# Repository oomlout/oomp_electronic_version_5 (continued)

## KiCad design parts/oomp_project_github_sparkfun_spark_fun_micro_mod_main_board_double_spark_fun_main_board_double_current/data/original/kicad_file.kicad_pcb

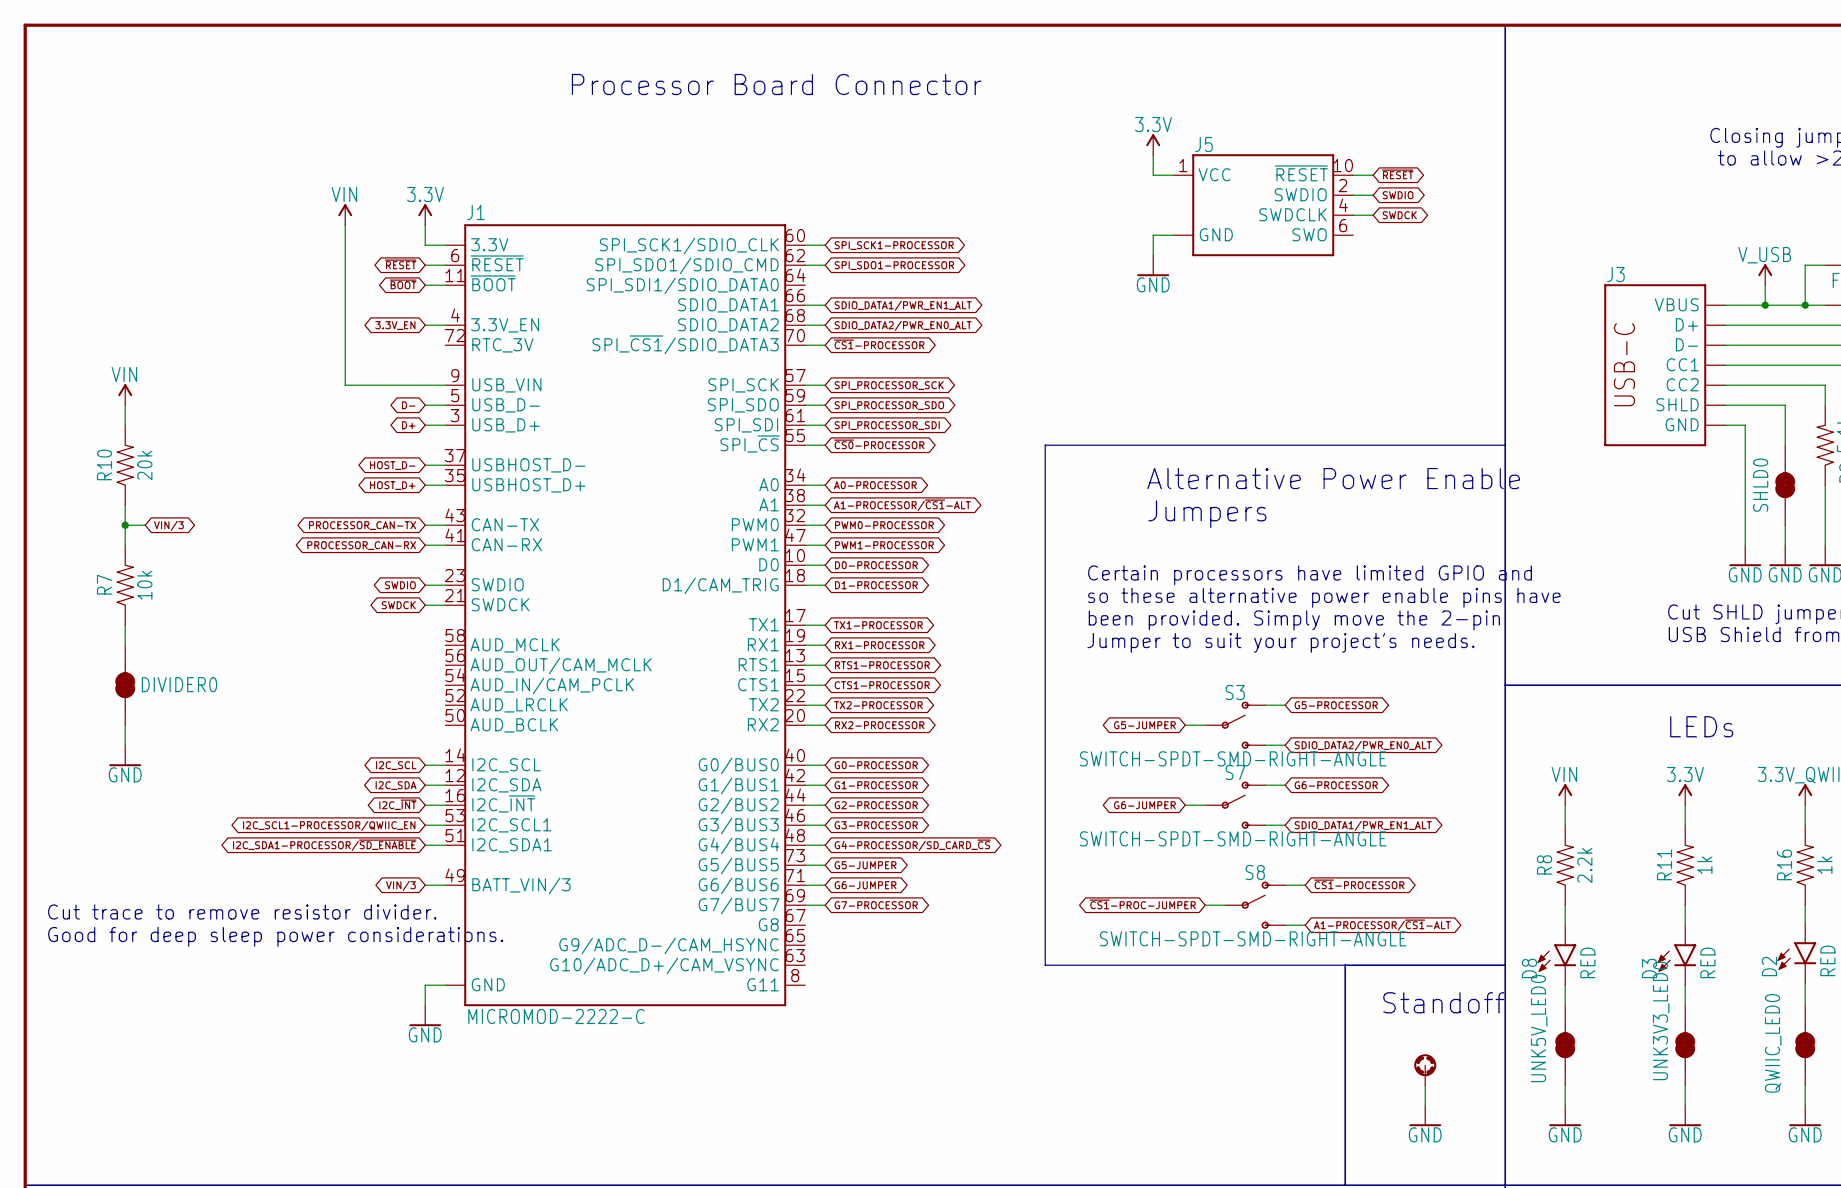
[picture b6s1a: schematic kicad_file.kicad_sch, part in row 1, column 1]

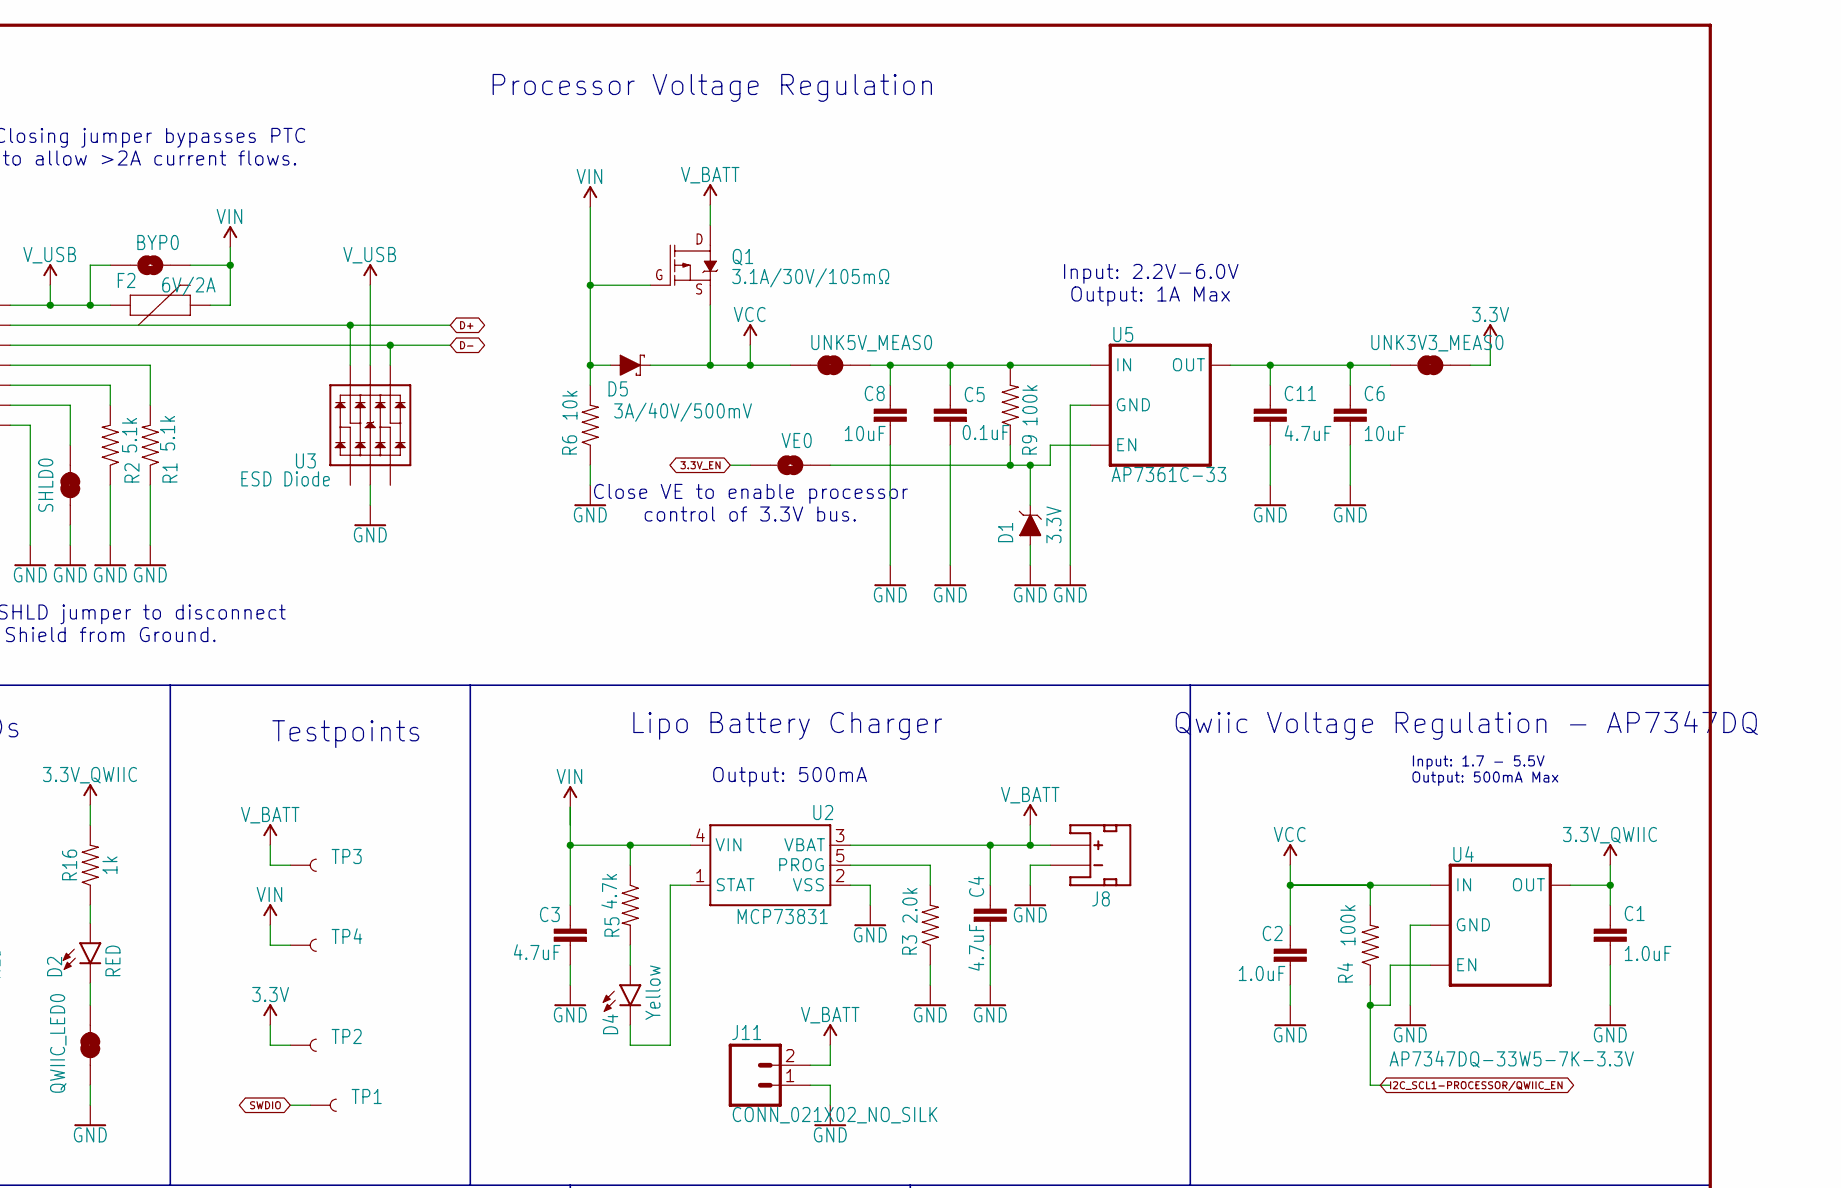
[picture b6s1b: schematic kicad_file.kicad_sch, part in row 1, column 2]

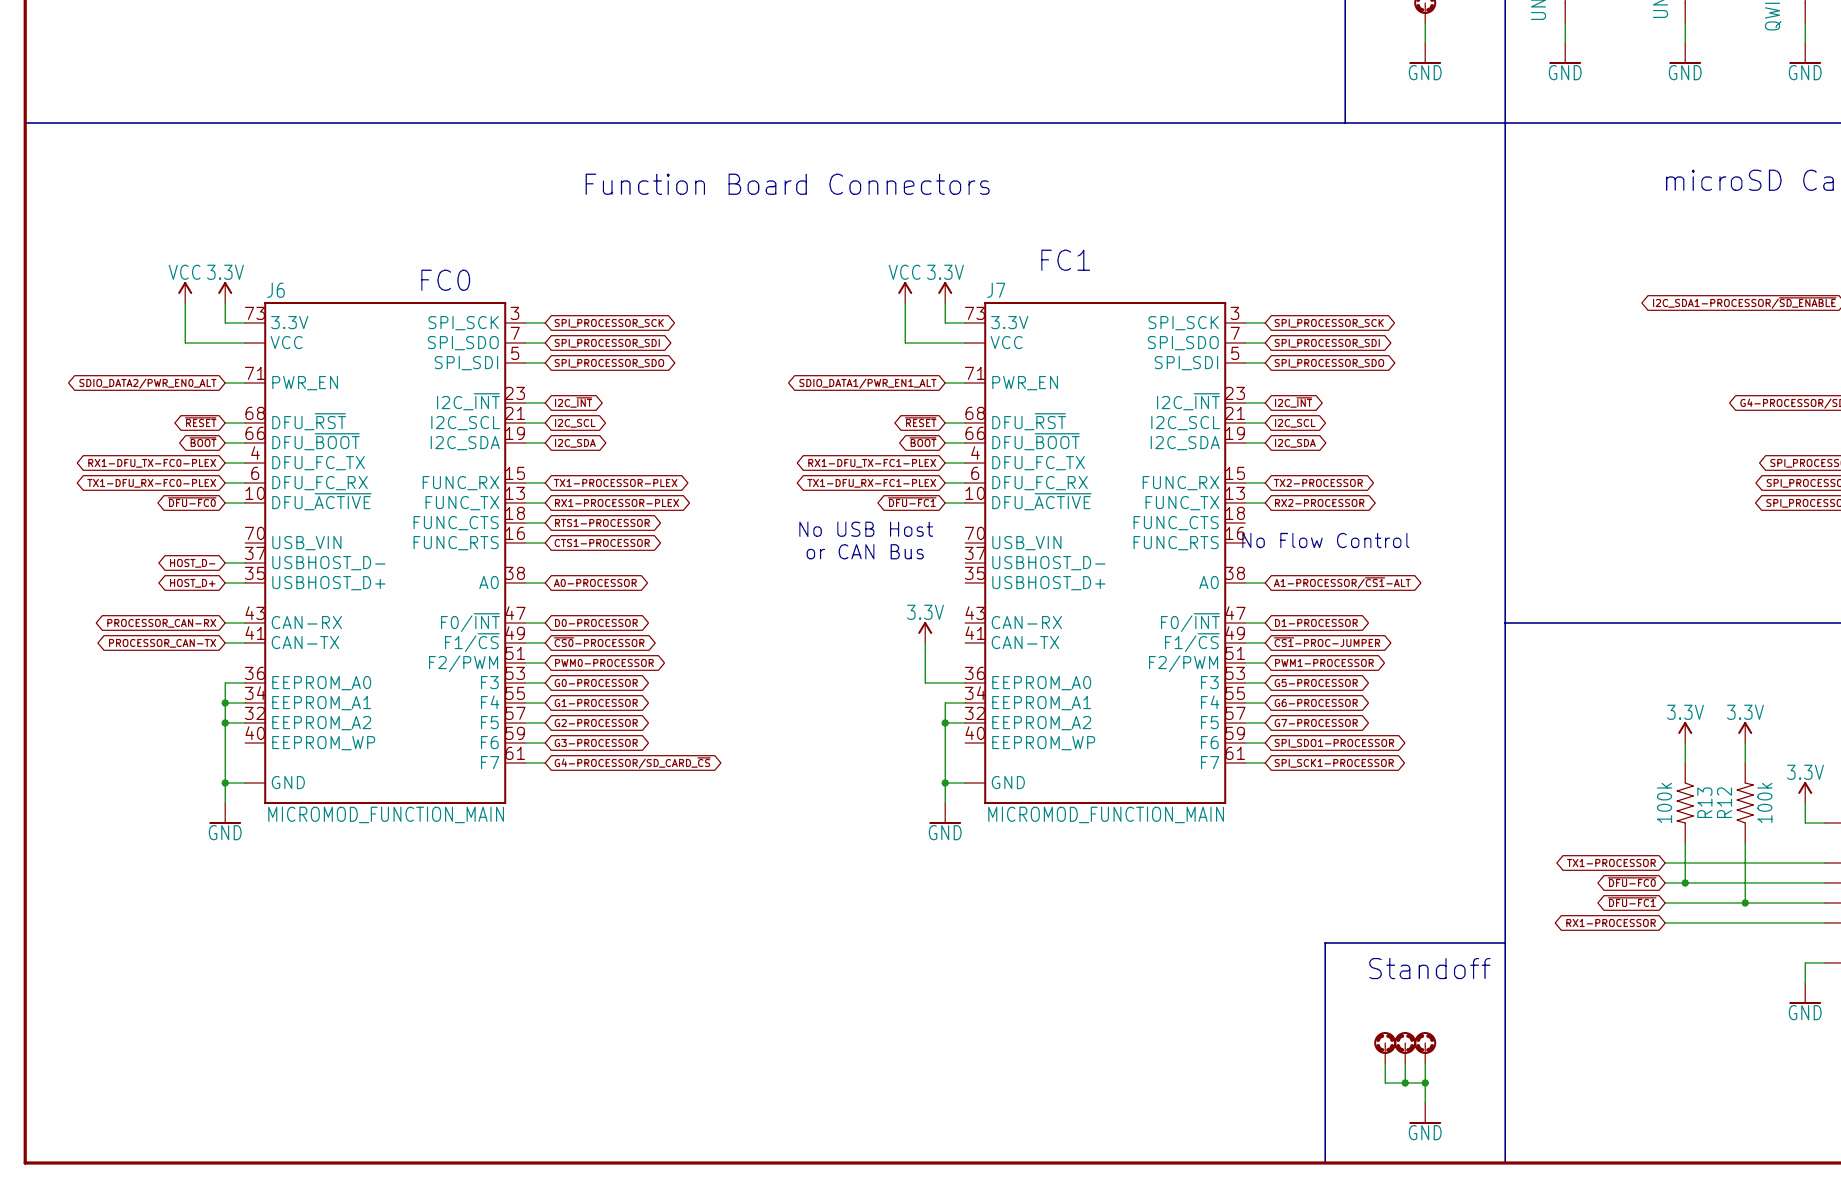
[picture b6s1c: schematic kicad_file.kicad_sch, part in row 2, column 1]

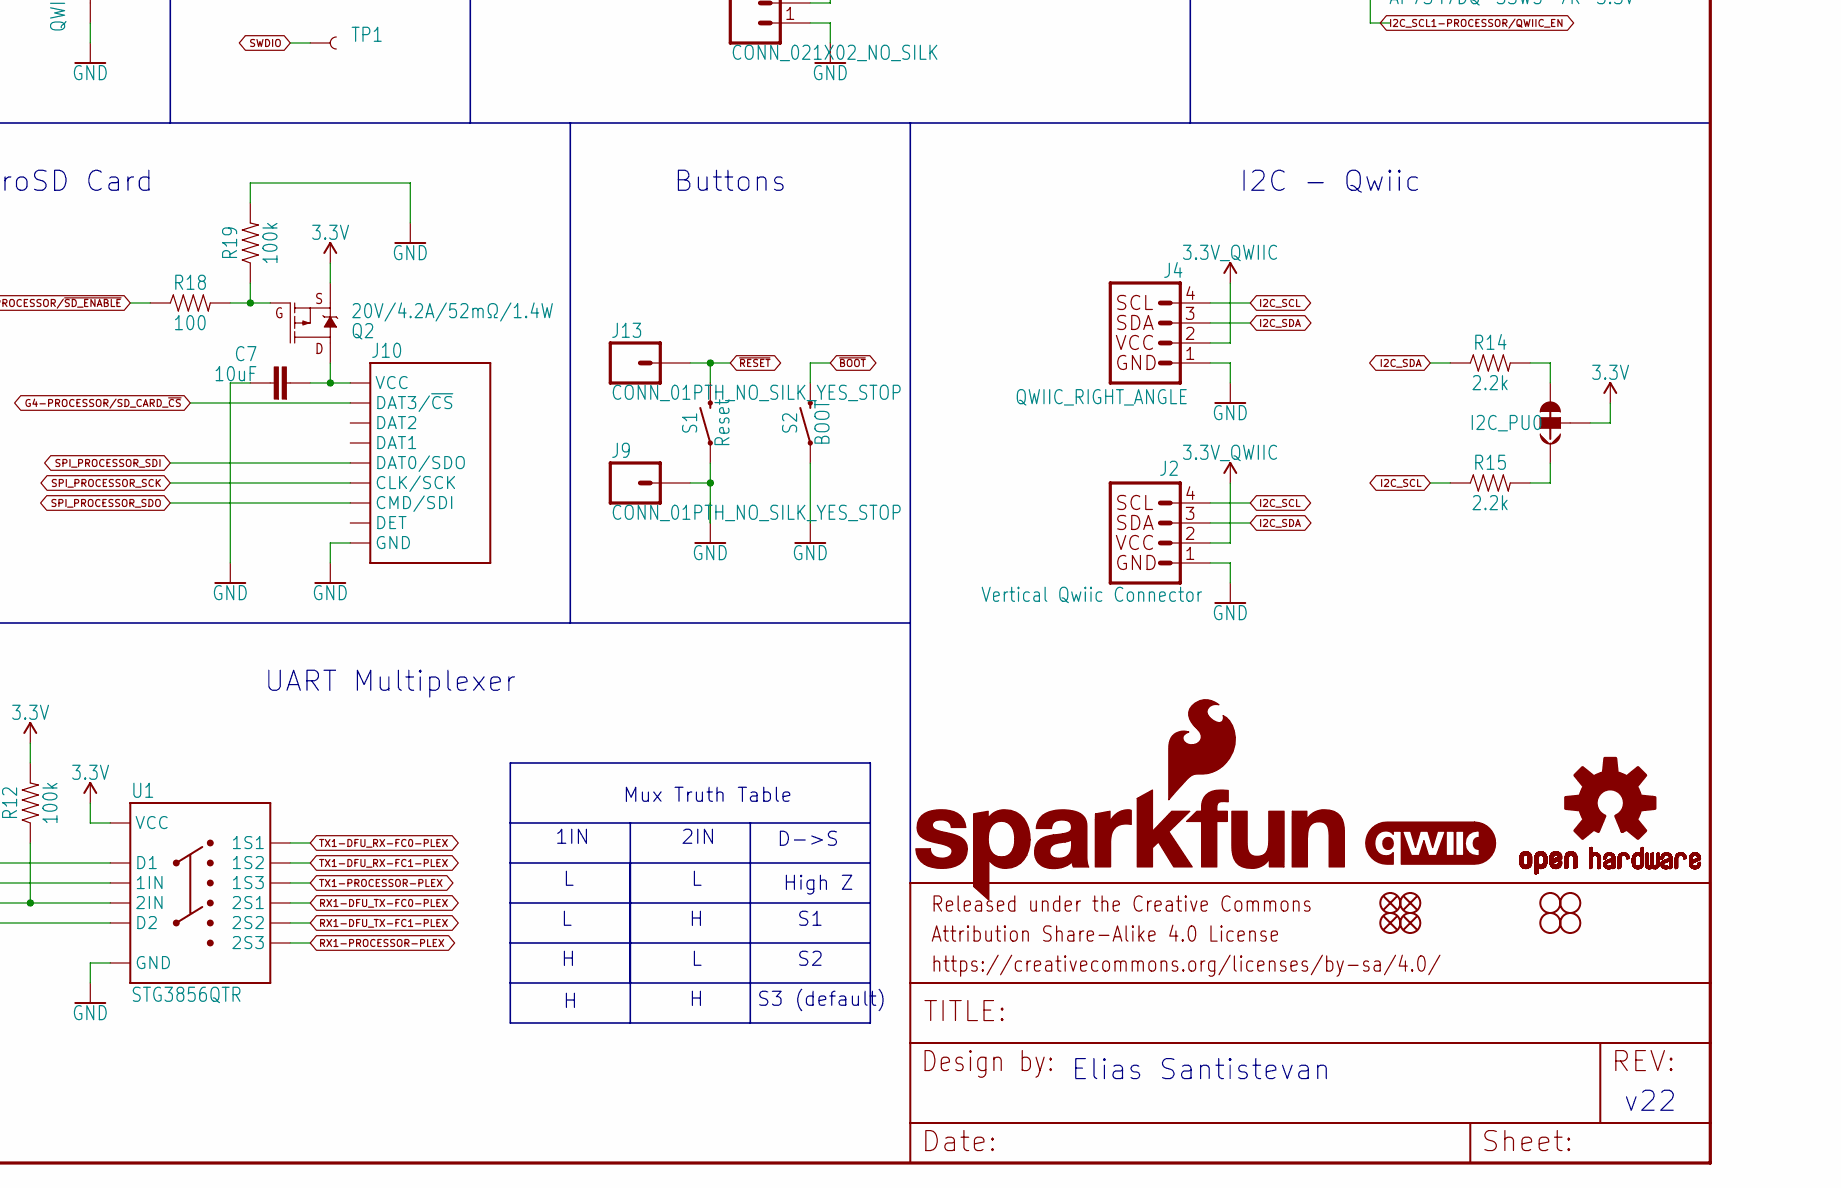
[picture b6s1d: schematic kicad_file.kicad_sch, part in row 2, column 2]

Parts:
BYP0: JUMPER-SMT_2_NO_SILK; SMT-JUMPER_2_NO_SILK
C1, C2: 1.0uF; 0603
C3, C4, C11: 4.7uF; 0603
C5: 0.1uF; 0603
C6, C8: 10uF; 0805
C7: 10uF; 0603
D1: 3.3V; SOD-323
D2, D3, D8: RED; LED-0603
D4: Yellow; LED-0603
D5: 3A/40V/500mV; SMA-DIODE
DIVIDER0: JUMPER-SMT_2_NC_TRACE_SILK; SMT-JUMPER_2_NC_TRACE_SILK
F2: 6V/2A; 1210
FD1, FD2, FD3, FD4: FIDUCIAL1X2; FIDUCIAL-1X2
FRAME1: FRAME-LEDGER; CREATIVE_COMMONS
H2, H3, H4, H8: STAND-OFF-REFLOW-M2.5_2.5MM_TALL; STAND-OFF-REFLOW-M2.5
H14, H15, H16, H17: STAND-OFFTIGHT; STAND-OFF-TIGHT
I2C_PU0: JUMPER-SMT_3_2-NC_TRACE_SILK; SMT-JUMPER_3_2-NC_TRACE_SILK
J1: MICROMOD-2222-C; M.2-CONNECTOR-E
J2: Vertical Qwiic Connector; JST04_1MM_VERT
J3: USB_C_2-LAYER_PADS; USB-C-16P-2LAYER-PADS
J4: QWIIC_RIGHT_ANGLE; JST04_1MM_RA
J5: CORTEX_JTAG_DEBUG_MINIMUM_PTH; 2X5-PTH-1.27MM
J6, J7: MICROMOD_FUNCTION_MAIN; M.2-CONNECTOR-E-FUNCTION-STANDARD
J8: JST_2MM_MALE; JST-2-SMD
J9, J13: CONN_01PTH_NO_SILK_YES_STOP; 1X01_NO_SILK
J10: MICRO-SD-PUSH-PUSH-EXT-PIN; MICROSD-EXTERNALPIN
J11: CONN_021X02_NO_SILK; 1X02_NO_SILK
LOGO1: QWIIC_LOGO_8MM; QWIIC_8MM
LOGO2: SFE_LOGO_NAME_FLAME.3_INCH; SFE_LOGO_NAME_FLAME_.3
LOGO3: OSHW-LOGOL; OSHW-LOGO-L
Q1: 3.1A/30V/105mΩ; SOT23-3
Q2: 20V/4.2A/52mΩ/1.4W; SOT23-3
QWIIC_LED0: JUMPER-SMT_2_NC_TRACE_SILK; SMT-JUMPER_2_NC_TRACE_SILK
R1, R2: 5.1k; 0603
R3: 2.0k; 0603
R4, R9, R12, R13, R19: 100k; 0603
R5: 4.7k; 0603
R6, R7: 10k; 0603
R8, R14, R15: 2.2k; 0603
R10: 20k; 0603
R11, R16: 1k; 0603
R18: 100; 0603
S1: Reset; TACTILE_SWITCH_SMD_5.2MM
S2: BOOT; TACTILE_SWITCH_SMD_5.2MM
S3, S7, S8: SWITCH-SPDT-SMD-RIGHT-ANGLE; SWITCH_SPST_SMD_A
SHLD0: JUMPER-SMT_2_NC_TRACE_SILK; SMT-JUMPER_2_NC_TRACE_SILK
TP1, TP2, TP3, TP4: TEST-POINT3X5; PAD.03X.05
U1: STG3856QTR; STG3856
U2: MCP73831; SOT23-5
U3: ESD Diode; SOT-23-6
U4: AP7347DQ-33W5-7K-3.3V; SOT25
U5: AP7361C-33; UDFN-8
UNK3V3_LED0, UNK5V_LED0: JUMPER-SMT_2_NC_TRACE_SILK; SMT-JUMPER_2_NC_TRACE_SILK
UNK3V3_MEAS0, UNK5V_MEAS0: JUMPER-COMBO_2_NC_TRACE; COMBO-JUMPER_2_NC_TRACE
VE0: JUMPER-SMT_2_NO_SILK; SMT-JUMPER_2_NO_SILK

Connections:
3.3V: I2C_PU0.2, J1.2 (3.3V), J1.74 (3.3V), J5.1 (VCC), J6.73 (3.3V), J7.36 (EEPROM_A0), J7.73 (3.3V), Q2.2 (S), R11.2, R12.2, R13.1, TP2.1, U1.P11 (VCC), UNK3V3_MEAS0.2, UNK3V3_MEAS0.4 (2)
3.3V_EN: J1.4 (3.3V_EN), VE0.1
3.3V_EN_VE: D1.C, R9.1, U5.5 (EN), VE0.2
3.3V_QWIIC: C1.1, J2.2, J4.2, R16.2, U4.5 (OUT)
3V3_MEAS: C6.1, C11.1, U5.1 (OUT), UNK3V3_MEAS0.1, UNK3V3_MEAS0.3 (1)
5V_MEAS: C5.1, C8.1, R9.2, U5.8 (IN), UNK5V_MEAS0.2, UNK5V_MEAS0.4 (2)
A0-PROCESSOR: J1.34 (A0), J6.38 (A0)
A1-PROCESSOR/~CS1-ALT: J1.38 (A1), J7.38 (A0), S8.3 (S)
CTS1-PROCESSOR: J1.15 (CTS1), J6.16 (FUNC_RTS)
D0-PROCESSOR: J1.10 (D0), J6.47 (F0/~INT)
D1-PROCESSOR: J1.18 (D1/CAM_TRIG), J7.47 (F0/~INT)
D+: J1.3 (USB_D+), J3.A6 (D+), J3.B6 (D+), U3.6 (IO4)
D-: J1.5 (USB_D-), J3.A7 (D-), J3.B7 (D-), U3.4 (IO3)
G0-PROCESSOR: J1.40 (G0/BUS0), J6.53 (F3)
G1-PROCESSOR: J1.42 (G1/BUS1), J6.55 (F4)
G2-PROCESSOR: J1.44 (G2/BUS2), J6.57 (F5)
G3-PROCESSOR: J1.46 (G3/BUS3), J6.59 (F6)
G4-PROCESSOR/SD_CARD_~CS: J1.48 (G4/BUS4), J6.61 (F7), J10.2 (DAT3/~CS)
G5-JUMPER: J1.73 (G5/BUS5), S3.2
G5-PROCESSOR: J7.53 (F3), S3.1 (O)
G6-JUMPER: J1.71 (G6/BUS6), S7.2
G6-PROCESSOR: J7.55 (F4), S7.1 (O)
G7-PROCESSOR: J1.69 (G7/BUS7), J7.57 (F5)
GND: C1.2, C2.2, C3.2, C4.2, C5.2, C6.2, C7.1, C8.2, C11.2, D1.A, DIVIDER0.1, H2.1, H3.1, H4.1, H8.1, J1.1 (GND), J1.7 (GND), J1.33 (GND), J1.36 (GND), J1.39 (GND), J1.45 (GND), J1.75 (GND), J2.1, J3.GND, J3.GND2 (GND), J4.1, J5.3 (GND), J5.5 (GND), J5.9 (GND), J6.1 (GND), J6.2 (GND), J6.8 (GND), J6.32 (EEPROM_A2), J6.33 (GND), J6.34 (EEPROM_A1), J6.36 (EEPROM_A0), J6.39 (GND), J6.45 (GND), J6.75 (GND), J7.1 (GND), J7.2 (GND), J7.8 (GND), J7.32 (EEPROM_A2), J7.33 (GND), J7.34 (EEPROM_A1), J7.39 (GND), J7.45 (GND), J7.75 (GND), J8.1 (-), J9.1, J10.6 (GND), J10.10 (GND), J10.11 (GND), J10.12 (GND), J10.13 (GND), J11.1, QWIIC_LED0.1, R1.1, R2.1, R3.1, R6.1, R19.2, S1.1, S1.2 (1), S2.1, S2.2 (1), SHLD0.1, U1.P5 (GND), U2.2 (VSS), U3.2 (VSS), U4.2 (GND), U5.4 (GND), U5.EP (GND), UNK3V3_LED0.1, UNK5V_LED0.1
HOST_D+: J1.35 (USBHOST_D+), J6.35 (USBHOST_D+)
HOST_D-: J1.37 (USBHOST_D-), J6.37 (USBHOST_D-)
I2C_SCL: J1.14 (I2C_SCL), J2.4, J4.4, J6.21 (I2C_SCL), J7.21 (I2C_SCL), R15.1
I2C_SCL1-PROCESSOR/QWIIC_EN: J1.53 (I2C_SCL1), R4.1, U4.3 (EN)
I2C_SDA: J1.12 (I2C_SDA), J2.3, J4.3, J6.19 (I2C_SDA), J7.19 (I2C_SDA), R14.1
I2C_SDA1-PROCESSOR/~SD_ENABLE: J1.51 (I2C_SDA1), R18.1
I2C_~INT: J1.16 (I2C_~INT), J6.23 (I2C_~INT), J7.23 (I2C_~INT)
unnamed: D4.A, R5.2
unnamed: D8.C, UNK5V_LED0.2
unnamed: D3.A, R11.1
unnamed: J3.B5 (CC2), R2.2
unnamed: J3.A5 (CC1), R1.2
unnamed: R3.2, U2.5 (PROG)
unnamed: DIVIDER0.2, R7.1
unnamed: D2.C, QWIIC_LED0.2
unnamed: D2.A, R16.1
unnamed: D3.C, UNK3V3_LED0.2
unnamed: I2C_PU0.3, R14.2
unnamed: D8.A, R8.1
unnamed: I2C_PU0.1, R15.2
unnamed: D4.C, U2.1 (STAT)
unnamed: C7.2, J10.4 (VCC), Q2.3 (D)
unnamed: Q2.1 (G), R18.2, R19.1
PROCESSOR_CAN-RX: J1.41 (CAN-RX), J6.43 (CAN-RX)
PROCESSOR_CAN-TX: J1.43 (CAN-TX), J6.41 (CAN-TX)
PWM0-PROCESSOR: J1.32 (PWM0), J6.51 (F2/PWM)
PWM1-PROCESSOR: J1.47 (PWM1), J7.51 (F2/PWM)
RTS1-PROCESSOR: J1.13 (RTS1), J6.18 (FUNC_CTS)
RX1-DFU_TX-FC0-PLEX: J6.4 (DFU_FC_TX), U1.P9 (2S1)
RX1-DFU_TX-FC1-PLEX: J7.4 (DFU_FC_TX), U1.P8 (2S2)
RX1-PROCESSOR: J1.19 (RX1), U1.P6 (D2)
RX1-PROCESSOR-PLEX: J6.13 (FUNC_TX), U1.P7 (2S3)
RX2-PROCESSOR: J1.20 (RX2), J7.13 (FUNC_TX)
SDIO_DATA1/PWR_EN1_ALT: J1.66 (SDIO_DATA1), J7.71 (PWR_EN), S7.3 (S)
SDIO_DATA2/PWR_EN0_ALT: J1.68 (SDIO_DATA2), J6.71 (PWR_EN), S3.3 (S)
SHLD: J3.SHLD1 (SHLD), J3.SHLD2 (SHLD), J3.SHLD3 (SHLD), J3.SHLD4 (SHLD), SHLD0.2
SPI_PROCESSOR_SCK: J1.57 (SPI_SCK), J6.3 (SPI_SCK), J7.3 (SPI_SCK), J10.5 (CLK/SCK)
SPI_PROCESSOR_SDI: J1.61 (SPI_SDI), J6.7 (SPI_SDO), J7.7 (SPI_SDO), J10.7 (DAT0/SDO)
SPI_PROCESSOR_SDO: J1.59 (SPI_SDO), J6.5 (SPI_SDI), J7.5 (SPI_SDI), J10.3 (CMD/SDI)
SPI_SCK1-PROCESSOR: J1.60 (SPI_SCK1/SDIO_CLK), J7.61 (F7)
SPI_SDO1-PROCESSOR: J1.62 (SPI_SDO1/SDIO_CMD), J7.59 (F6)
SWDCK: J1.21 (SWDCK), J5.4 (SWDCLK)
SWDIO: J1.23 (SWDIO), J5.2 (SWDIO), TP1.1
TX1-DFU_RX-FC0-PLEX: J6.6 (DFU_FC_RX), U1.P1 (1S1)
TX1-DFU_RX-FC1-PLEX: J7.6 (DFU_FC_RX), U1.P2 (1S2)
TX1-PROCESSOR: J1.17 (TX1), U1.P4 (D1)
TX1-PROCESSOR-PLEX: J6.15 (FUNC_RX), U1.P3 (1S3)
TX2-PROCESSOR: J1.22 (TX2), J7.15 (FUNC_RX)
VCC: C2.1, D5.C, J6.72 (VCC), J6.74 (VCC), J7.72 (VCC), J7.74 (VCC), Q1.2 (S), R4.2, U4.1 (IN), UNK5V_MEAS0.1, UNK5V_MEAS0.3 (1)
VIN: BYP0.2, C3.1, D5.A, F2.2, J1.9 (USB_VIN), Q1.1 (G), R5.1, R6.2, R8.2, R10.2, TP4.1, U2.4 (VIN)
VIN/3: J1.49 (BATT_VIN/3), R7.2, R10.1
V_BATT: C4.1, J8.2 (+), J11.2, Q1.3 (D), TP3.1, U2.3 (VBAT)
V_USB: BYP0.1, F2.1, J3.VBUS1 (VBUS), J3.VBUS2 (VBUS), U3.5 (VCC)
~BOOT: J1.11 (~BOOT), J6.66 (DFU_~BOOT), J7.66 (DFU_~BOOT), S2.3 (2), S2.4 (2)
~CS0-PROCESSOR: J1.55 (SPI_~CS), J6.49 (F1/~CS)
~CS1-PROC-JUMPER: J7.49 (F1/~CS), S8.2
~CS1-PROCESSOR: J1.70 (SPI_~CS1/SDIO_DATA3), S8.1 (O)
~DFU-FC0: J6.10 (DFU_~ACTIVE), R13.2, U1.P12 (1IN)
~DFU-FC1: J7.10 (DFU_~ACTIVE), R12.1, U1.P10 (2IN)
~RESET: J1.6 (~RESET), J5.10 (~RESET), J6.68 (DFU_~RST), J7.68 (DFU_~RST), J13.1, S1.3 (2), S1.4 (2)

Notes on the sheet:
Close VE to enable processor control of 3.3V bus.
v22
Certain processors have limited GPIO and so these alternative power enable pins have been provided. Simply move the 2-pin Jumper to suit your project's needs.
S3 (default)
Output: 500mA
Standoff
Input: 1.7 - 5.5V Output: 500mA Max
Alternative Power Enable Jumpers
No USB Host or CAN Bus
UART Multiplexer
Function Board Connectors
Qwiic Voltage Regulation - AP7347DQ
Buttons
2IN
No Flow Control
1IN
LEDs
I2C - Qwiic
Cut SHLD jumper to disconnect USB Shield from Ground.
Closing jumper bypasses PTC to allow >2A current flows.
Elias Santistevan
Input: 2.2V-6.0V Output: 1A Max
Mux Truth Table
Cut trace to remove resistor divider. Good for deep sleep power considerations.
Processor Voltage Regulation
FC0
Lipo Battery Charger
Processor Board Connector
D->S
Testpoints
High Z
microSD Card
FC1

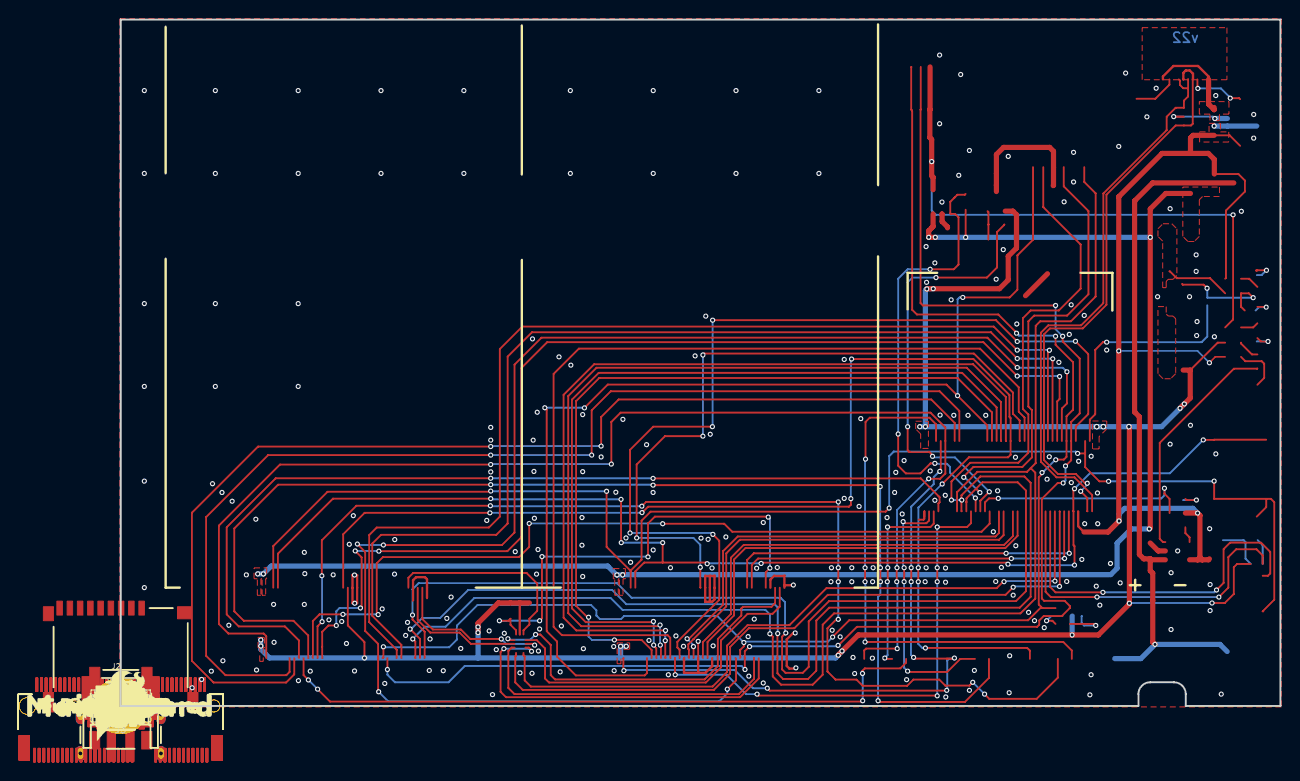
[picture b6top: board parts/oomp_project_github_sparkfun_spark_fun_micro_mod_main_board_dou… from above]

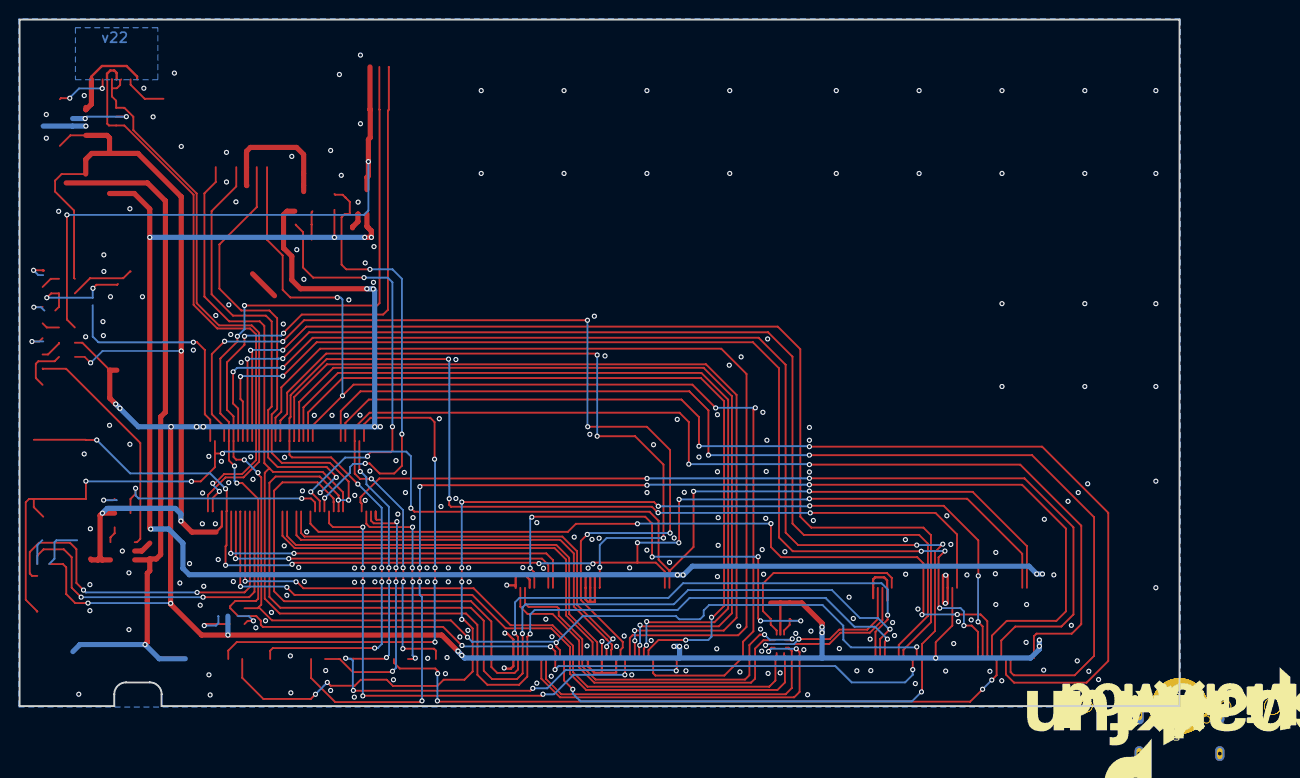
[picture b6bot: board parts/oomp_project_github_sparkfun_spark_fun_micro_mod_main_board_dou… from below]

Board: 2 copper layers, 124.5 x 73.7 mm, 136 parts (27 on the bottom side), 84 nets.

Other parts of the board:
FRAME2: FRAME-LEDGERNO_FOOTPRINT; DUMMY
H1: STAND-OFFTIGHT; STAND-OFF-TIGHT
U$1: #3V3_LED#22
U$2: #3V3_EN#23
U$3: ##RST##8
U$4: 3V332533
U$5: VIN32532
U$6: CHG32531
U$7: #SHLD#501
U$8: BOOT32541
U$9: RESET32540
U$10: PROCESSOR525
U$11: FUNCTION_ZERO520
U$12: FUNCTION_ONE524
U$13: MAIN523
U$14: MICROMOD_MI_LOGO_1
U$15: 0523
U$16: 1524
U$17: MICROMOD_LOGO_1
U$18: BOARD524
U$19: G518
U$20: #CS_ALT#20
U$21: MAIN_BOARD5523
U$22: QWIIC_3MM
U$23: STANDOFF501
U$24: SFE_LOGO_FLAME_.3
U$25: SWD6522
U$26: #3V3_MEAS#6522
U$27: CHARGE501
U$28: #QWIIC_LED#22
U$29: G6519
U$30: #I2C#501
U$31: #5V_MEAS#6522
U$32: CS17
U$33: 500MA6520
U$34: #CS_DEF#19
U$35: #G5_PROC#21
U$36: #G6_PROC#21
U$37: #EN0_ALT#21
U$38: #EN1_ALT#21
U$39, U$40: #GND#10
U$41: #DIVIDER#23
U$42: #VIN_LED#24
U$43: QWC18
U$44: SFE_LOGO_NAME_FLAME_.1
U$45: #PTC#13
U$46: #VBAT#9
